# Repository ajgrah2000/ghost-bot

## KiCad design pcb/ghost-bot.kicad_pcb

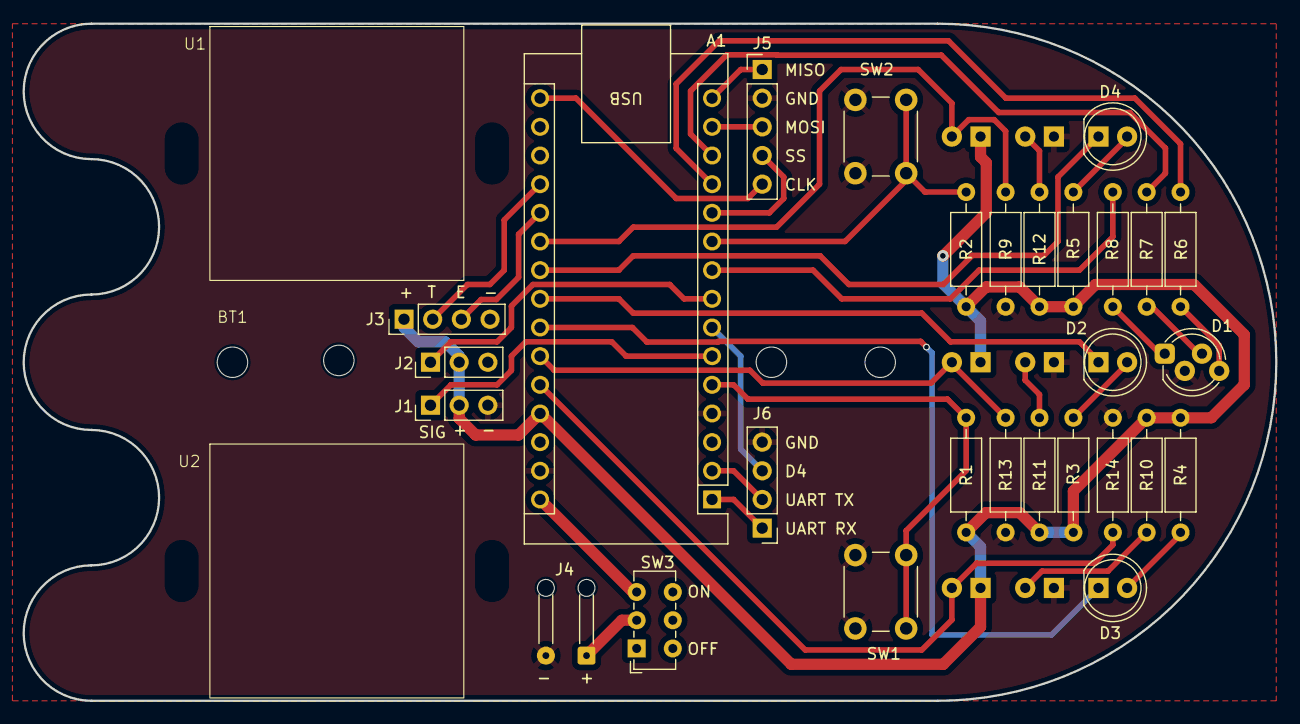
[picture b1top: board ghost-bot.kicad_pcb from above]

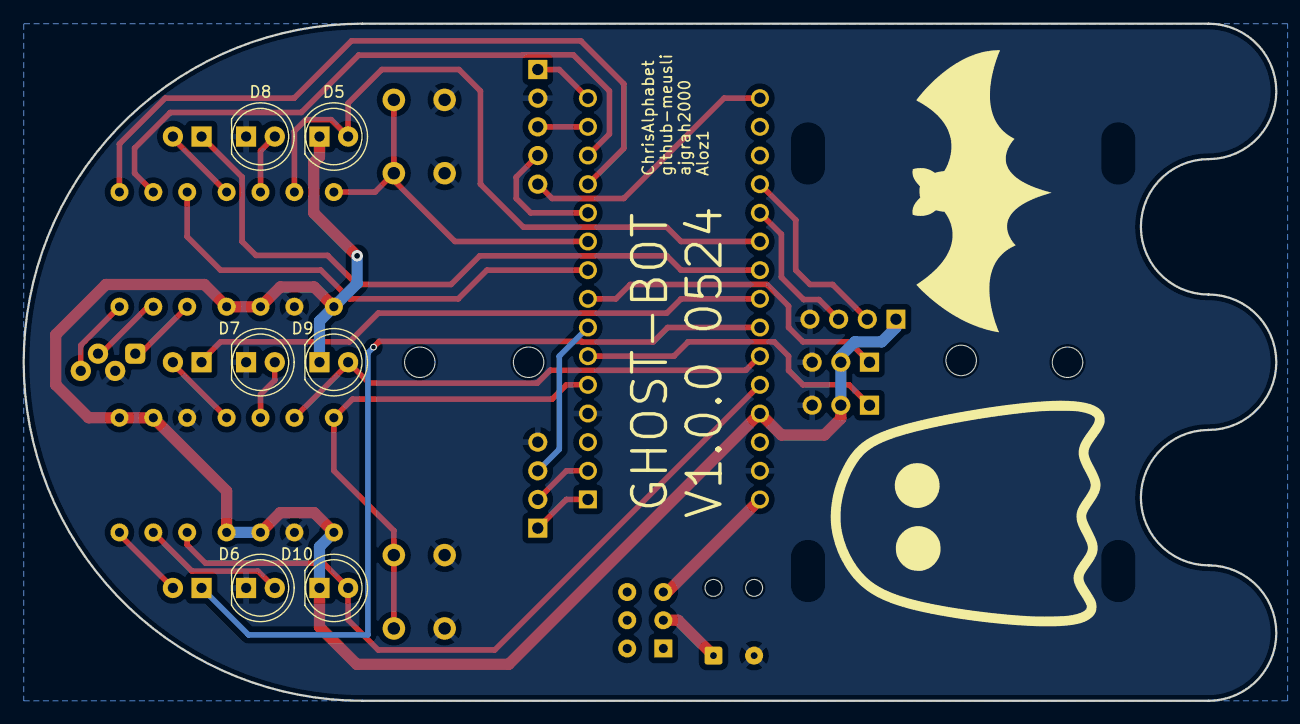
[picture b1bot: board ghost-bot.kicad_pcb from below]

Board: 2 copper layers, 111.0 x 60.0 mm, 37 parts (6 on the bottom side), 35 nets.

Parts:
A1: Arduino_Nano_v3.x; Arduino_Nano
BT1: Battery Holder; Keystone 2478 Battery Holder
D1: LED_BKGR; LED_D5.0mm-4_RGB_Staggered_Pins
D2, D3, D4: LED; LED_D5.0mm
D5, D9, D10: D_Photo; LED_D5.0mm_Clear
D6, D7, D8: IR LED; LED_D5.0mm_IRBlack
J1, J2: Conn_01x03_Pin; PinHeader_1x03_P2.54mm_Vertical
J3, J6: Conn_01x04_Pin; PinHeader_1x04_P2.54mm_Vertical
J4: Conn_01x02_Pin; SolderWire-0.1sqmm_1x02_P3.6mm_D0.4mm_OD1mm_Relief
J5: Conn_01x05_Pin; PinHeader_1x05_P2.54mm_Vertical
R1, R2: 10k; R_Axial_DIN0207_L6.3mm_D2.5mm_P10.16mm_Horizontal
R3, R4, R5: 330R; R_Axial_DIN0207_L6.3mm_D2.5mm_P10.16mm_Horizontal
R6: 150R; R_Axial_DIN0207_L6.3mm_D2.5mm_P10.16mm_Horizontal
R7, R8, R10, R11, R12: 100R; R_Axial_DIN0207_L6.3mm_D2.5mm_P10.16mm_Horizontal
R9, R13, R14: 100k; R_Axial_DIN0207_L6.3mm_D2.5mm_P10.16mm_Horizontal
SW1, SW2: SW_Push; SW_PUSH_6mm
SW3: Switch; SW_E-Switch_EG1271_SPDT
U1: SG90 Mount Left
U2: SG90 Mount Right

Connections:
+5V: A1.27 (+5V), D5.1 (K), D9.1 (K), D10.1 (K), J1.2, J2.2, J3.1, R1.2, R2.2, R3.1, R4.1, R5.1, R10.1, R11.1, R12.1
+BATT: J4.1, SW3.2 (B)
+BATT_SW: A1.30 (VIN), SW3.3 (A)
/ECHO: A1.20 (A1), J3.3
/GPIO_D4: A1.7 (D4), J6.3
/LED0: A1.23 (A4), D2.1 (K)
/LED1: A1.24 (A5), D3.1 (K)
/LED2: A1.22 (A3), D4.1 (K)
/PD0: A1.21 (A2), D5.2 (A), R9.2
/PD1: A1.25 (A6), D9.2 (A), R13.2
/PD2: A1.26 (A7), D10.2 (A), R14.2
/PUSH_BTN0: A1.5 (D2), R1.1, SW1.2
/PUSH_BTN1: A1.10 (D7), R2.1, SW2.2
/RGB_B: A1.9 (D6), R8.2
/RGB_G: A1.13 (D10), R7.2
/RGB_R: A1.12 (D9), R6.2
/SERVO0: A1.6 (D3), J1.1
/SERVO1: A1.8 (D5), J2.1
/SPI_CLK: A1.16 (D13), J5.5
/SPI_MISO: A1.15 (D12), J5.1
/SPI_MOSI: A1.14 (D11), J5.3
/SPI_SS: A1.11 (D8), J5.4
/TRIG: A1.19 (A0), J3.2
/UART_RX: A1.1 (D1/TX), J6.1
/UART_TX: A1.2 (D0/RX), J6.2
GND: A1.4 (GND), A1.29 (GND), D1.2 (K), D6.1 (K), D7.1 (K), D8.1 (K), J1.3, J2.3, J3.4, J4.2, J5.2, J6.4, R9.1, R13.1, R14.1, SW1.1, SW2.1
unnamed: D1.1 (BA), R8.1
unnamed: D1.3 (GA), R7.1
unnamed: D1.4 (RA), R6.1
unnamed: D2.2 (A), R3.2
unnamed: D3.2 (A), R4.2
unnamed: D4.2 (A), R5.2
unnamed: D6.2 (A), R10.2
unnamed: D7.2 (A), R11.2
unnamed: D8.2 (A), R12.2

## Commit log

2024-09-27 Issue: Fix LED1 pin: Attempted to swap A5 and A6 in schematic and PCB (although not sure what I may of broken in the mean time).
2025-01-08 Adding an attempt to generate blender render outputs.
2025-01-09 Adding missed github action update.
2025-01-10 Switched rotation axis to be a symetrical one.
2025-01-10 Removing the need for the 'empty.blend' file
2025-01-11 Switching render to 'eevee', added a dummy display so githubactions would work.
